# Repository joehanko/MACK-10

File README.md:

# MACK-10 Tensile Tester

> An open-source desktop tensile tester for affordable material characterization and education.

---

# Overview

MACK-10 is an open-source desktop tensile tester designed to measure the force and displacement of small material specimens.

The project combines an ESP32-based controller, load cell, stepper-driven linear stage, custom PCB, and 3D-printed components to create a low-cost alternative to commercial material testing equipment.

The target capacity is **10 kg (~98 N)**, making MACK-10 suitable for testing:

- 3D-printed plastics
- Engineering polymers
- Composites
- Thin metals
- Educational material samples

---

# Current Status

🚧 **Prototype Development — Revision 1**

## Electronics

- [x] Custom KiCad controller PCB
- [x] ESP32 controller
- [x] HX711 load cell interface
- [x] TMC2208 stepper driver
- [x] LM2596 power regulation
- [x] OLED interface
- [x] E-stop input
- [x] Dual limit switch inputs
- [x] PlatformIO firmware
- [x] Automatic taring
- [x] Peak force tracking
- [x] Break detection
- [x] Live serial plotting

## Mechanical

- [x] 200 mm T6×1 linear motion stage
- [x] NEMA 11 stepper drive
- [ ] Structural frame
- [ ] Load cell mount
- [ ] Specimen grips
- [ ] Electronics enclosure

## In Development

- [ ] Load cell calibration
- [ ] Crosshead speed control
- [ ] Position tracking
- [ ] Force-displacement logging
- [ ] Stress-strain calculations
- [ ] CSV export

---

# Target Specifications

| Specification  | Target                    |
| -------------- | ------------------------- |
| Maximum Force  | 10 kg (~98 N)             |
| Load Cell      | 10 kg S-Type              |
| Controller     | ESP32                     |
| Motion         | NEMA 11 + T6×1 Lead Screw |
| Travel         | 200 mm                    |
| User Interface | 128×64 OLED               |
| PCB            | Custom KiCad Design       |
| Firmware       | PlatformIO                |

---

# Bill of Materials

## Electronics

|   Qty | Component                     | Approx. Cost | Line Total |
| ----: | ----------------------------- | -----------: | ---------: |
|     1 | ESP32 DevKit V1               |        $8.00 |      $8.00 |
|     1 | Custom MACK-10 Controller PCB |        $1.08 |      $1.08 |
|     1 | HX711 Load Cell Amplifier     |        $3.00 |      $3.00 |
|     1 | TMC2208 Stepper Driver        |        $5.00 |      $5.00 |
|     1 | LM2596 Buck Converter         |        $2.00 |      $2.00 |
|     1 | 10 kg S-Type Load Cell        |       $25.00 |     $25.00 |
|     1 | SSD1306 128×64 OLED           |        $5.00 |      $5.00 |
|     1 | PCB Fuse Holder               |        $1.00 |      $1.00 |
|     1 | 2–2.5 A Fuse                  |        $0.50 |      $0.50 |
|     1 | Power Switch                  |        $3.00 |      $3.00 |
|     1 | Emergency Stop Switch         |       $12.00 |     $12.00 |
|     2 | Limit Switches                |        $2.00 |      $4.00 |
| 1 Set | JST-XH Connectors & Crimps    |        $4.00 |      $4.00 |
| 1 Set | Female Header Sockets         |        $2.00 |      $2.00 |
|     — | LEDs, Resistors & Capacitors  |       ~$2.00 |     ~$2.00 |
|     — | Wire, Heat Shrink & Misc.     |       ~$5.00 |     ~$5.00 |

**Estimated Electronics Cost: ~$83**

## Mechanical

| Qty | Component                        | Approx. Cost | Line Total |
| --: | -------------------------------- | -----------: | ---------: |
|   1 | T6×1 Linear Motion Stage, 200 mm |       $31.99 |     $31.99 |
|   1 | NEMA 11 Stepper Motor            |     Included |   Included |
|   1 | T6×1 Lead Screw                  |     Included |   Included |
|   1 | Linear Guide & Carriage          |     Included |   Included |
|   1 | Structural Frame Hardware        |      ~$20.00 |    ~$20.00 |
|   1 | Grip Hardware                    |      ~$20.00 |    ~$20.00 |
|   1 | M3 Fastener Kit                  |      ~$10.00 |    ~$10.00 |
|   1 | M3 Heat-Set Inserts              |       ~$5.00 |     ~$5.00 |
|   — | Filament                         |      ~$20.00 |    ~$20.00 |

**Estimated Mechanical Cost: ~$107**

**Current Estimated Build Cost: ~$190 + power supply and miscellaneous hardware**

---

---

# Repository Structure

```text
firmware/    ESP32 firmware
pcb/         KiCad project files
cad/         Mechanical CAD models
docs/        Documentation
images/      Project photos and diagrams
```

---

# Roadmap

### Revision 1

Complete the mechanical assembly, calibrate the load cell, and perform initial tensile tests.

### Revision 2

Optimize the PCB, wiring, enclosure, motion control, and data acquisition.

### Revision 3

Add automated testing, material property calculations, and desktop software.

---

# Disclaimer

MACK-10 is intended for educational and hobby use and is not a replacement for calibrated or certified laboratory testing equipment.

Measurements should not be used for engineering certification, regulatory compliance, or safety-critical design decisions.

---

**Project Status:** Active Development 🚧

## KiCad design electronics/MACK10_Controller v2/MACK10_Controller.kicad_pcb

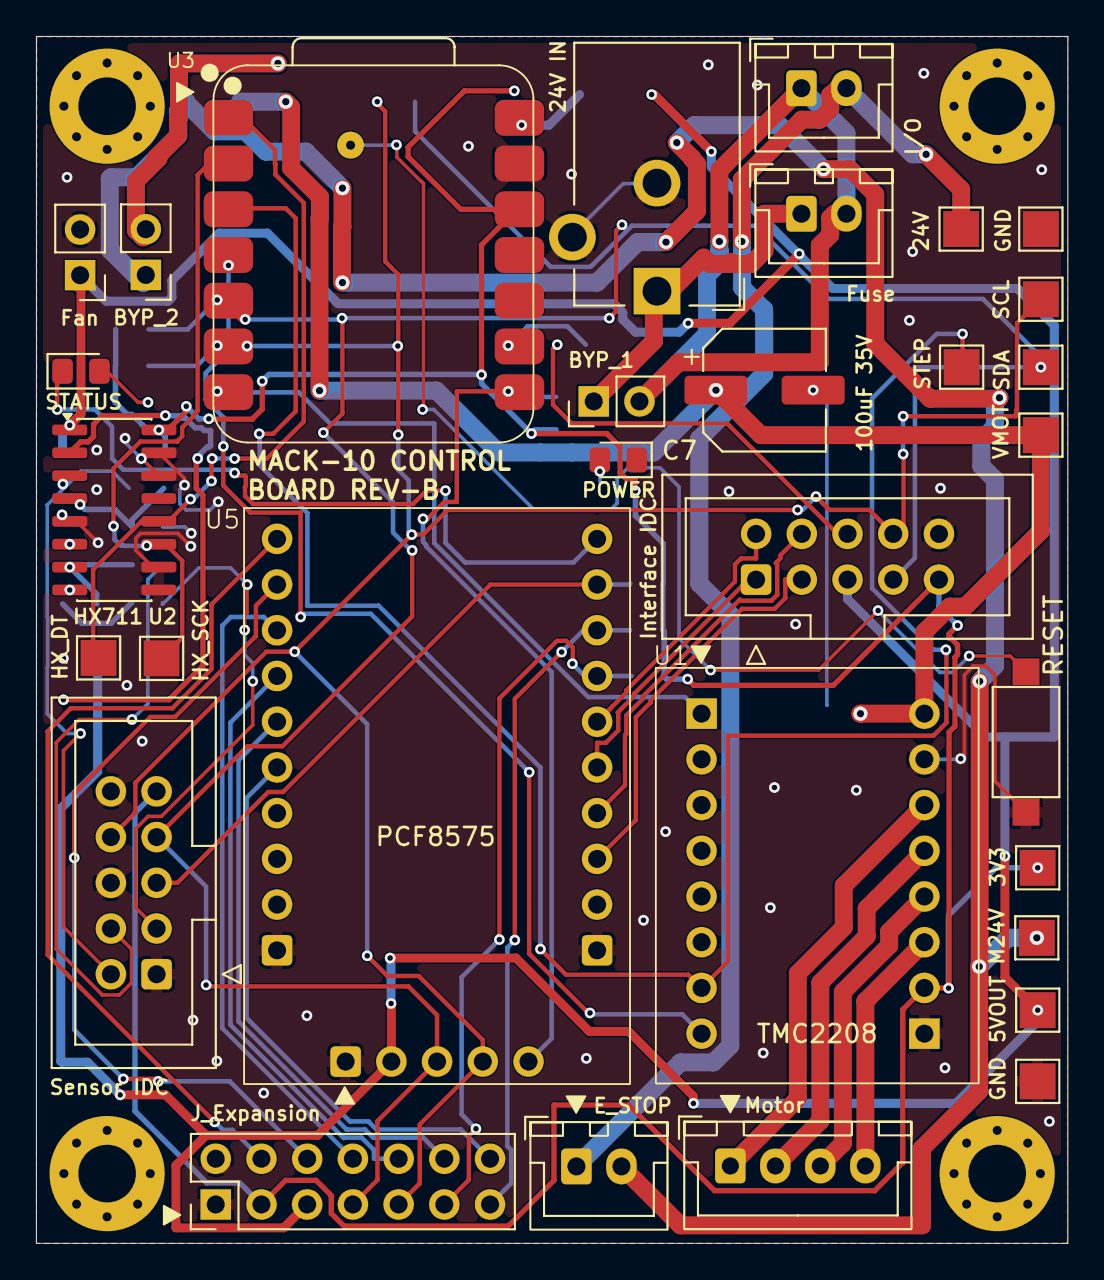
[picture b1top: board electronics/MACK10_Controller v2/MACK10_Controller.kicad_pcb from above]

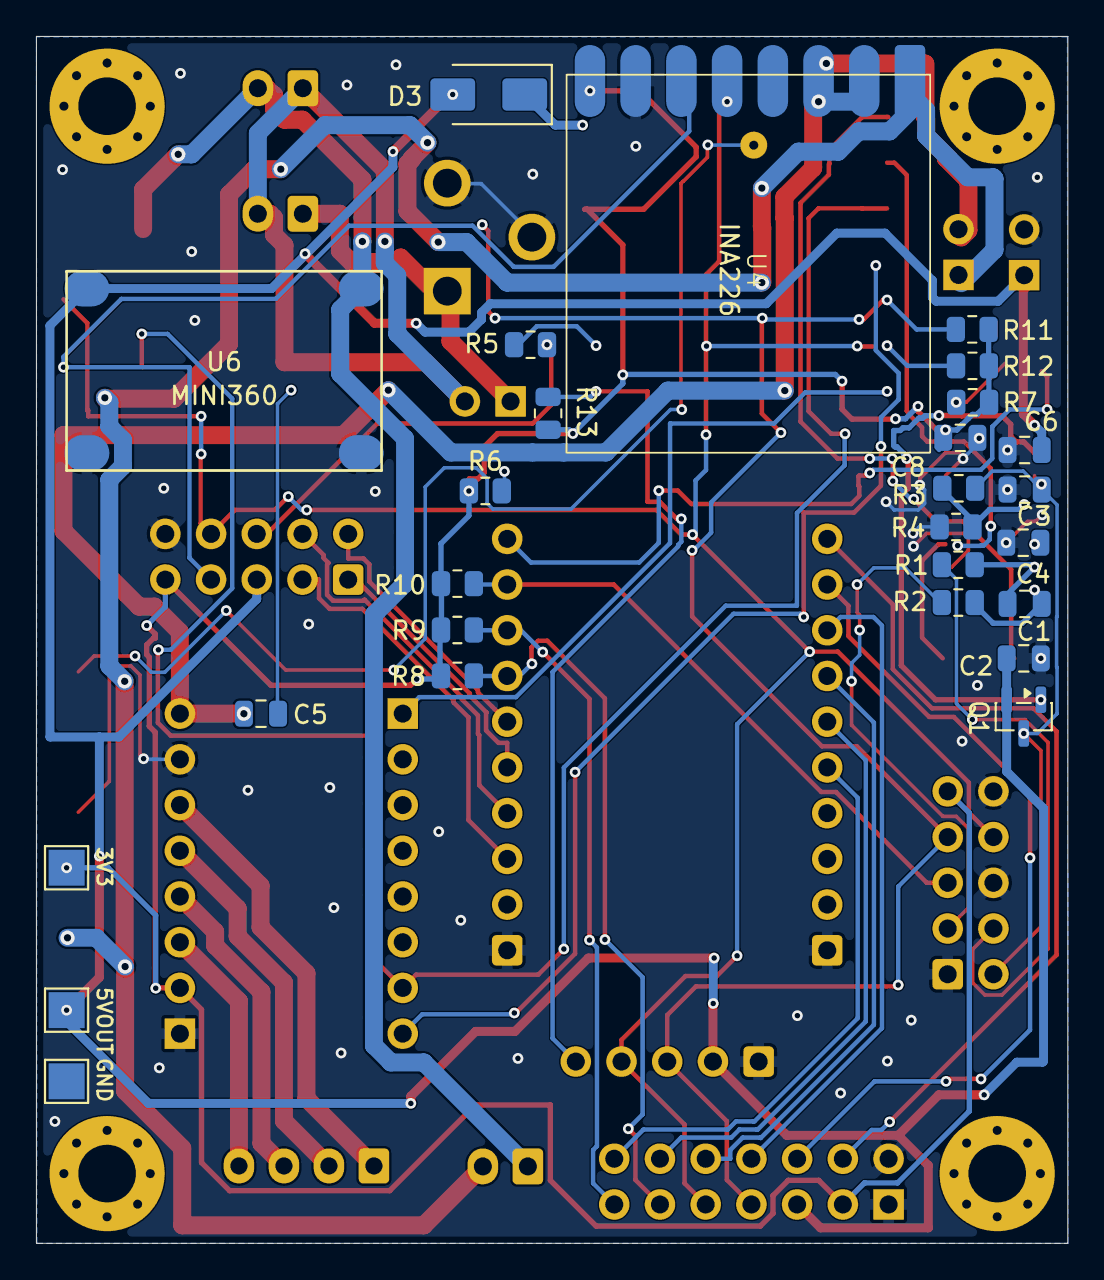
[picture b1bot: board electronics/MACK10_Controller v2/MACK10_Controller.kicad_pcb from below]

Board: 2 copper layers, 57.3 x 67.1 mm, 62 parts (27 on the bottom side), 49 nets.

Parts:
C1, C4, C6, C8: 0.1uF; C_0805_2012Metric
C2, C3: 10uF; C_0805_2012Metric
C5: 100nF 50V; C_0805_2012Metric
C7: 100uF 35V; CP_Elec_6.3x7.7
D1: POWER; LED_0805_2012Metric_Pad1.15x1.40mm_HandSolder
D2: STATUS; LED_0805_2012Metric_Pad1.15x1.40mm_HandSolder
D3: SS14; D_SMA
F1: Fuse; JST_XH_B2B-XH-A_1x02_P2.50mm_Vertical
J2: Motor; JST_XH_B4B-XH-A_1x04_P2.50mm_Vertical
J3: J_Expansion; PinHeader_2x07_P2.54mm_Vertical
J4: I/O; JST_XH_B2B-XH-A_1x02_P2.50mm_Vertical
J5: Sensor IDC; IDC-Header_2x05_P2.54mm_Vertical
J6: Interface IDC; IDC-Header_2x05_P2.54mm_Vertical
J7: Fan; PinHeader_1x02_P2.54mm_Vertical
J8: E_STOP; JST_XH_B2B-XH-A_1x02_P2.50mm_Vertical
J9: 24V IN; BarrelJack_CUI_PJ-102AH_Horizontal
J10: BYP_2; PinHeader_1x02_P2.54mm_Vertical
JP1: BYP_1; PinHeader_1x02_P2.54mm_Vertical
Mount 1, Mount 2, Mount 3, Mount 4: MountingHole_3.2mm_M3_Pad_Via
Q1: SS8550; SOT-23
R1, R2: 100; R_0805_2012Metric
R3: 18k; R_0805_2012Metric
R4: 7.5k; R_0805_2012Metric
R5: 470; R_0805_2012Metric
R6, R7: 1k; R_0805_2012Metric
R8, R9, R10, R13: 10k; R_0805_2012Metric
R11, R12: 4.7k, DNP; R_0805_2012Metric
SW1: RESET; SW_SPST_CK_RS282G05A3
TP1: STEP; TestPoint_Pad_2.0x2.0mm
TP2: HX_DT; TestPoint_Pad_2.0x2.0mm
TP3: HX_SCK; TestPoint_Pad_2.0x2.0mm
TP4: SDA; TestPoint_Pad_2.0x2.0mm
TP5: SCL; TestPoint_Pad_2.0x2.0mm
TP6: VMOT; TestPoint_Pad_2.0x2.0mm
TP7: M24V; TestPoint_Pad_2.0x2.0mm
TP8, TP8#2: 3V3; TestPoint_Pad_2.0x2.0mm
TP9: 24V; TestPoint_Pad_2.0x2.0mm
TP10, TP10#2: 5VOUT; TestPoint_Pad_2.0x2.0mm
TP11, TP11#2, TP11#3: GND; TestPoint_Pad_2.0x2.0mm
U1: TMC2208; TMC2208_STEPSTICK
U2: HX711; SOIC-16_3.9x9.9mm_P1.27mm
U3: XIAO-C6; XIAO-ESP32-C6-SMD
U4: INA226
U5: PCF8575
U6: MINI360; Mini360_step-down

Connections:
/3V3: C8.1, J3.3, J5.9, J6.9, R6.1, R7.1, R8.1, R9.1, R10.1, R11.1, R12.1, R13.1, TP8.1 (1_1), TP8#2.1 (1_1), U1.15 (VIO), U2.16 (DVDD), U3.12 (3V3_OUT), U4.8 (VCC)
/24VIN: F1.1, J9.1, JP1.1 (A)
/+5V: C2.2, C6.1, D3.2 (A), J3.5, J6.5, J7.1, Q1.2 (E), TP10.1 (1_1), TP10#2.1 (1_1), U2.1 (VSUP), U5.2 (VCC), U6.4 (VOUT+)
/+24V: J4.2, J8.1, TP9.1 (1_1), U6.2 (VIN+)
/A+: J5.3, R2.1
/A-: J5.4, R1.1
/DIR: U1.8 (DIR), U3.4 (D3)
/DOWN: J6.4, U5.9 (P01)
/E+: C3.1, J5.2, Q1.3 (C), R3.2, U2.3 (AVDD)
/ENABLE: U1.1 (EN), U3.7 (D6)
/E_STOP_SENSE: J5.5, R10.2, U5.14 (P06)
/GND: C2.1, C3.2, C4.1, C6.2, C8.2, D1.1 (K), J3.1, J3.2, J5.1, J5.6, J5.10, J6.10, J7.2, J9.2, J9.3, R4.1, SW1.1, TP11.1 (1_1), U1.10 (GND), U1.16 (GND), U2.5 (AGND), U2.9 (INB-), U2.10 (INB+), U2.14 (XI), U2.15 (RATE), U3.13 (GND), U4.7 (GND), U5.1 (GND), U5.6 (GND), U5.25 (GND), U6.1 (VIN-), U6.3 (VOUT-)
/HX711_DT: TP2.1 (1_1), U2.12 (DOUT), U3.1 (D0)
/HX711_SCK: TP3.1 (1_1), U2.11 (PD_SCK), U3.2 (D1)
/IO1: J3.4, U5.16 (P10)
/IO2: J3.6, U5.17 (P11)
/IO3: J3.8, U5.18 (P12)
/IO4: J3.10, U5.19 (P13)
/IO5: J3.12, U5.20 (P14)
/IO6: J3.14, U5.21 (P15)
/LEFT: J6.2, U5.11 (P03)
/LIM_BOT: J3.13, R9.2, U5.13 (P05)
/LIM_TOP: J3.11, R8.2, U5.12 (P04)
/MOTOR_24V: J8.2, J10.1, TP7.1 (1_1), U4.1 (IN+)
/MOTOR_VMOT: C5.1, C7.1, J10.2, TP6.1 (1_1), U1.9 (VMOT), U4.2 (IN-), U4.3 (VBUS)
/PCF_INT: R13.2, U3.8 (D7), U5.5 (INT)
/RGB_STATUS: R5.1, U3.9 (D8)
/RIGHT: J6.1, U5.10 (P02)
/SCL: J3.9, J5.8, J6.8, R12.2, TP5.1 (1_1), U3.6 (D5), U4.5 (SCL), U5.4 (SCL)
/SDA: J3.7, J5.7, J6.7, R11.2, TP4.1 (1_1), U3.5 (D4), U4.6 (SDA), U5.3 (SDA)
/STATUS: D2.1 (K), U5.15 (P07)
/STEP: TP1.1 (1_1), U1.7 (STEP), U3.3 (D2)
/UP: J6.3, U5.8 (P00)
/USER_LED: J6.6, R5.2
unnamed: C5.2, C7.2
unnamed: D1.2 (A), R6.2
unnamed: D2.2 (A), R7.2
unnamed: D3.1 (K), U3.14 (VBUS)
unnamed: F1.2, J4.1, JP1.2 (B)
unnamed: J2.1, U1.11 (1B)
unnamed: J2.2, U1.12 (1A)
unnamed: J2.3, U1.13 (2A)
unnamed: J2.4, U1.14 (2B)
unnamed: Q1.1 (B), U2.2 (BASE)
unnamed: C1.2, R2.2, U2.8 (INA+)
unnamed: C1.1, R1.2, U2.7 (INA-)
unnamed: C4.2, U2.6 (VBG)
unnamed: R3.1, R4.2, U2.4 (VFB)
unnamed: SW1.2, U3.17 (EN)

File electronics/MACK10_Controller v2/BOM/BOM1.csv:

"Reference","Qty","Value","DNP","Exclude from BOM","Exclude from Board","Footprint","Datasheet"
"C1,C4,C6,C8","4","0.1uF","","","","Capacitor_SMD:C_0805_2012Metric",""
"C2,C3","2","10uF","","","","Capacitor_SMD:C_0805_2012Metric",""
"C5","1","100nF 50V","","","","Capacitor_SMD:C_0805_2012Metric",""
"C7","1","100uF 35V","","","","Capacitor_SMD:CP_Elec_6.3x7.7",""
"D1","1","POWER","","","","LED_SMD:LED_0805_2012Metric_Pad1.15x1.40mm_HandSolder",""
"D2","1","STATUS","","","","LED_SMD:LED_0805_2012Metric_Pad1.15x1.40mm_HandSolder",""
"D3","1","SS14","","","","Diode_SMD:D_SMA","http://www.vishay.com/docs/88525/1n5817.pdf"
"F1","1","Fuse","","","","Connector_JST:JST_XH_B2B-XH-A_1x02_P2.50mm_Vertical",""
"J2","1","Motor","","","","Connector_JST:JST_XH_B4B-XH-A_1x04_P2.50mm_Vertical",""
"J3","1","J_Expansion","","","","Connector_PinHeader_2.54mm:PinHeader_2x07_P2.54mm_Vertical",""
"J4","1","I/O","","","","Connector_JST:JST_XH_B2B-XH-A_1x02_P2.50mm_Vertical",""
"J5","1","Sensor IDC","","","","Connector_IDC:IDC-Header_2x05_P2.54mm_Vertical",""
"J6","1","Interface IDC","","","","Connector_IDC:IDC-Header_2x05_P2.54mm_Vertical",""
"J7","1","Fan","","","","Connector_PinHeader_2.54mm:PinHeader_1x02_P2.54mm_Vertical",""
"J8","1","E_STOP","","","","Connector_JST:JST_XH_B2B-XH-A_1x02_P2.50mm_Vertical",""
"J9","1","24V IN","","","","Connector_BarrelJack:BarrelJack_CUI_PJ-102AH_Horizontal",""
"J10","1","BYP_2","","","","Connector_PinHeader_2.54mm:PinHeader_1x02_P2.54mm_Vertical",""
"JP1","1","BYP_1","","","","Connector_PinHeader_2.54mm:PinHeader_1x02_P2.54mm_Vertical",""
"Q1","1","SS8550","","","","Package_TO_SOT_SMD:SOT-23","http://www.secosgmbh.com/datasheet/products/SSMPTransistor/S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"
"R1,R2","2","100","","","","Resistor_SMD:R_0805_2012Metric",""
"R3","1","18k","","","","Resistor_SMD:R_0805_2012Metric",""
"R4","1","7.5k","","","","Resistor_SMD:R_0805_2012Metric",""
"R5","1","470","","","","Resistor_SMD:R_0805_2012Metric",""
"R6,R7","2","1k","","","","Resistor_SMD:R_0805_2012Metric",""
"R8,R9,R10,R13","4","10k","","","","Resistor_SMD:R_0805_2012Metric",""
"R11,R12","2","4.7k, DNP","","","","Resistor_SMD:R_0805_2012Metric",""
"SW1","1","RESET","","","","Button_Switch_SMD:SW_SPST_CK_RS282G05A3",""
"TP1","1","STEP","","","","TestPoint:TestPoint_Pad_2.0x2.0mm",""
"TP2","1","HX_DT","","","","TestPoint:TestPoint_Pad_2.0x2.0mm",""
"TP3","1","HX_SCK","","","","TestPoint:TestPoint_Pad_2.0x2.0mm",""
"TP4","1","SDA","","","","TestPoint:TestPoint_Pad_2.0x2.0mm",""
"TP5","1","SCL","","","","TestPoint:TestPoint_Pad_2.0x2.0mm",""
"TP6","1","VMOT","","","","TestPoint:TestPoint_Pad_2.0x2.0mm",""
"TP7","1","M24V","","","","TestPoint:TestPoint_Pad_2.0x2.0mm",""
"TP8","1","3V3","","","","TestPoint:TestPoint_Pad_2.0x2.0mm",""
"TP9","1","24V","","","","TestPoint:TestPoint_Pad_2.0x2.0mm",""
"TP10","1","5VOUT","","","","TestPoint:TestPoint_Pad_2.0x2.0mm",""
"TP11","1","GND","","","","TestPoint:TestPoint_Pad_2.0x2.0mm",""
"U1","1","TMC2208","","","","MACK10:TMC2208_STEPSTICK",""
"U2","1","HX711","","","","Package_SO:SOIC-16_3.9x9.9mm_P1.27mm","https://web.archive.org/web/20220615044707/https://akizukide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"
"U3","1","XIAO-C6","","","","XIAO-SEEDSTUDIO:XIAO-ESP32-C6-SMD",""
"U4","1","INA226","","","","MACK10:INA226",""
"U5","1","PCF8575","","","","MACK10:PCF8575",""
"U6","1","MINI360","","","","Mini360:Mini360_step-down",""

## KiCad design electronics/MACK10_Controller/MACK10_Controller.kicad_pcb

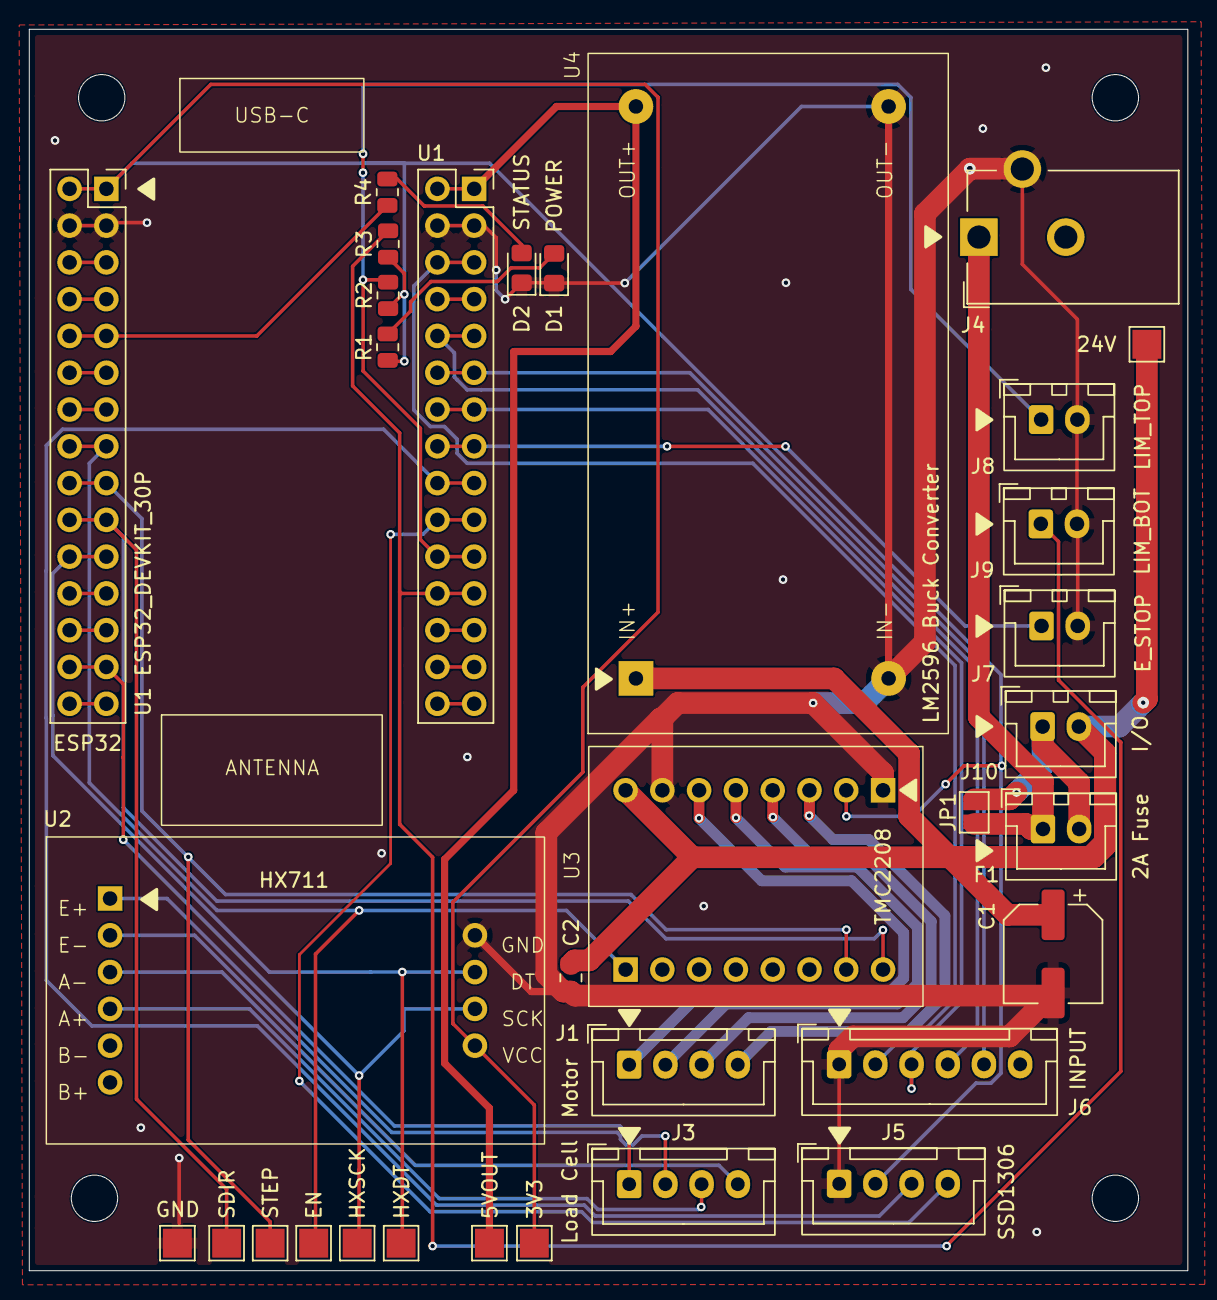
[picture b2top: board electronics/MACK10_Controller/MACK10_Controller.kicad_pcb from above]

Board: 2 copper layers, 80.0 x 85.7 mm, 36 parts (0 on the bottom side), 31 nets.

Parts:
C1: 100uF 35V; CP_Elec_6.3x7.7
C2: 100nF 50V; C_0805_2012Metric
D1: POWER; LED_0805_2012Metric_Pad1.15x1.40mm_HandSolder
D2: STATUS; LED_0805_2012Metric_Pad1.15x1.40mm_HandSolder
F1: 2A Fuse; JST_XH_B2B-XH-A_1x02_P2.50mm_Vertical
J1: Motor; JST_XH_B4B-XH-A_1x04_P2.50mm_Vertical
J3: Load Cell; JST_XH_B4B-XH-A_1x04_P2.50mm_Vertical
J4: 24V IN; BarrelJack_CUI_PJ-102AH_Horizontal
J5: SSD1306; JST_XH_B4B-XH-A_1x04_P2.50mm_Vertical
J6: INPUT; JST_XH_B6B-XH-A_1x06_P2.50mm_Vertical
J7: E_STOP; JST_XH_B2B-XH-A_1x02_P2.50mm_Vertical
J8: LIM_TOP; JST_XH_B2B-XH-A_1x02_P2.50mm_Vertical
J9: LIM_BOT; JST_XH_B2B-XH-A_1x02_P2.50mm_Vertical
J10: I/O; JST_XH_B2B-XH-A_1x02_P2.50mm_Vertical
JP1: FUSE_BYPASS; SolderJumper-2_P1.3mm_Open_Pad1.0x1.5mm
Mount 1, Mount 2, Mount 3, Mount 4: MountingHole_3.2mm_M3
R1, R4: 1k; R_0805_2012Metric
R2, R3: 10k; R_0805_2012Metric
TP1: 3V3; TestPoint_Pad_2.0x2.0mm
TP2: HXDT; TestPoint_Pad_2.0x2.0mm
TP3: 5VOUT; TestPoint_Pad_2.0x2.0mm
TP4: GND; TestPoint_Pad_2.0x2.0mm
TP5: 24V; TestPoint_Pad_2.0x2.0mm
TP6: HXSCK; TestPoint_Pad_2.0x2.0mm
TP7: EN; TestPoint_Pad_2.0x2.0mm
TP8: STEP; TestPoint_Pad_2.0x2.0mm
TP9: SDIR; TestPoint_Pad_2.0x2.0mm
U1: U1 ESP32_DEVKIT_30P; ESP32_DEVKIT_30PIN
U2: HX711; HX711_MODULE
U3: TMC2208; TMC2208_STEPSTICK
U4: LM2596 Buck Converter; LM2596_BUCK_CONVERTER

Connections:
/3V3: J5.2, R1.1, R2.1, R3.1, TP1.1 (1_1), U1.1 (3V3), U2.10 (VCC), U3.15 (VIO)
/24VIN: F1.1, J4.1, JP1.1 (A)
/+5V: TP3.1 (1_1), U1.16 (VIN), U4.3 (OUT+)
/+24V: C1.1, C2.1, J10.2, TP5.1 (1_1), U3.9 (VMOT), U4.1 (IN+)
/BACK: J6.5, U1.21 (D27)
/DIR: TP9.1 (1_1), U1.10 (D19), U3.8 (DIR)
/DOWN: J6.3, U1.22 (D26)
/ENABLE: TP7.1 (1_1), U1.8 (D5), U3.1 (EN)
/ESP32 D4: R4.1, U1.5 (D4)
/ESP32 D25: J7.1, U1.23 (D25)
/ESP32 D32: J5.4, U1.25 (D32)
/ESP32 D33: J5.3, U1.24 (D33)
/ESP32 D34: J9.1, R3.2, U1.27 (D34)
/ESP32 D35: J8.1, R2.2, U1.26 (D35)
/GND: C1.2, C2.2, D1.1 (K), D2.1 (K), J4.3, J5.1, J6.1, J7.2, J8.2, J9.2, TP4.1 (1_1), U1.2 (GND), U1.17 (GND), U2.7 (GND), U3.10 (GND), U3.16 (GND), U4.2 (IN-), U4.4 (OUT-)
/HX711_DT: TP2.1 (1_1), U1.11 (D21), U2.8 (DT)
/HX711_SCK: TP6.1 (1_1), U1.14 (D22), U2.9 (SCK)
/LOAD_A+: J3.3, U2.4 (A+)
/LOAD_A-: J3.4, U2.3 (A-)
/LOAD_E+: J3.1, U2.1 (E+)
/LOAD_E-: J3.2, U2.2 (E-)
/SELECT: J6.4, U1.20 (D14)
/STEP: TP8.1 (1_1), U1.9 (D18), U3.7 (STEP)
/UP: J6.2, U1.18 (D13)
unnamed: D1.2 (A), R1.2
unnamed: D2.2 (A), R4.2
unnamed: F1.2, J10.1, JP1.2 (B)
unnamed: J1.1, U3.11 (1B)
unnamed: J1.2, U3.12 (1A)
unnamed: J1.3, U3.13 (2A)
unnamed: J1.4, U3.14 (2B)
